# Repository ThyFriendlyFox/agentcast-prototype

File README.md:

# Agentcast

An HDMI dongle with a far-field mic array. Plug it into any TV; people in
the room talk, a cloud agent does the work, and the TV shows the results.
The product spec is [`docs/office-agent-dongle.md`](docs/office-agent-dongle.md).

## Hardware versions

| Version | State | Boards | Notes |
|---|---|---|---|
| [v0.5](hardware/v0.5/) | in work | an 80 x 30 mm, 8-layer stick with our own computer (ESP32-P4), LT8912B HDMI bridge, ESP32-C6 Wi-Fi, XUNPU HDMI-003 male plug, mic, mute, USB-C power and USB-C mic port | Not yet ordered: firmware and the LT8912B crystal value are open. |
| [v0.4](hardware/v0.4/) | archived | the v0.3 stick with a male HDMI Type-A plug on its end: plugs straight into the TV | Gates GREEN. Plug footprint awaits the plug's drawing (4 numbers). Not yet ordered. |
| [v0.3](hardware/v0.3/) | archived | one board, 67 x 46 mm stick: CM5 carrier, HDMI-A at the end, USB-C power and USB-C external mic on the sides, on-board mic, hardware mute | Gates GREEN. CM5 position checked against Raspberry Pi's 3D model. Fab files in `hardware/v0.3/dongle/fab/`. Not yet ordered. |
| [v0.2](hardware/v0.2/) | archived | one board, 57 x 50.4 mm: CM5 carrier, HDMI-A, USB-C power, USB-C port for an external mic, on-board mic, hardware mute | Gates GREEN. Fab files in `hardware/v0.2/dongle/fab/`. Not yet ordered. |
| [v0.1](hardware/v0.1/) | archived | main (CM5 carrier) and mic bar (4 mics) on a cable | Gates GREEN on both boards. Never ordered. |

## Tools

The boards are designed as code and checked with the
[Via EE Workcenter](https://github.com/ThyFriendlyFox/via): KiCad 10,
ngspice and FreeRouting, driven by `workcenter`. Each board folder holds a
`design.py`; the KiCad files beside it are generated from it.

```bash
make verify
```

## How work is run

[`agent-kit/ROUTING.md`](agent-kit/ROUTING.md) says which file governs
which job. Agents read [`CLAUDE.md`](CLAUDE.md) first.

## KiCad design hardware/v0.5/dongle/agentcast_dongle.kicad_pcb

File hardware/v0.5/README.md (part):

# Agentcast dongle v0.5

> **In work.** Made from [v0.4](../v0.4/) (commit `223e73b`). v0.5 drops the
> Raspberry Pi CM5 and puts our own small computer on a Chromecast-sized stick.

One board, **80 x 30 mm**, 8 layers, parts on both faces. A male HDMI plug
(XUNPU HDMI-003) clamps one end; the Wi-Fi antenna is at the other.

| | v0.4 | v0.5 |
|---|---|---|
| Size | 67 x 46 mm | 80 x 30 mm |
| Computer | Raspberry Pi CM5 module (55 x 40 mm, Linux) | ESP32-P4 (10 x 10 mm, 32 MB PSRAM in the package, no Linux) |
| HDMI | from the CM5 | LT8912B MIPI DSI to HDMI bridge, with HDMI audio |
| Wi-Fi | the CM5's | ESP32-C6-MINI-1 module (Wi-Fi 6), SDIO to the P4 |
| HDMI plug footprint | HDMI Type-A layout, 4 numbers unconfirmed | the XUNPU HDMI-003 drawing, every number |
| Layers | 4 | 8 (F.Cu, In1 GND, In2-In5, In6 GND, B.Cu), JLCPCB JLC081611-2116 |

| Top | Bottom | Turning |
|---|---|---|
|  |  |  |

Schematic: [`dongle/docs/schematic.png`](dongle/docs/schematic.png).

## Why no full computer

The dongle's jobs (spec, "How it works") are: hear the room and stream it to
the cloud agent, show what the agent made on the TV, and play the agent's
voice. The cloud does the thinking. None of that needs Linux or a browser on
the stick:

| Job | v0.5 |
|---|---|
| Hear the room | ICS-43434 I2S mic (or a USB mic on J6), streamed over Wi-Fi |
| Show the work | The cloud renders the dashboard and sends frames (JPEG, decoded by the P4's hardware JPEG codec); the P4 drives HDMI through DSI at 720p60 or 1080p30 |
| Speak | I2S audio into the LT8912B, out over HDMI to the TV's speakers |
| Echo cancellation | Mic capture and HDMI playback run on the same I2S clock (one BCLK, one WS) |
| Mute | SW2 cuts the power of both mics; LIVE / MUTED LEDs run from the switch |

What it gives up: the stick cannot run a web page by itself, so the cloud
renders the screen. A 2-lane DSI link at 1.5 Gb/s per lane (ESP32-P4 datasheet
4.2.1.7) carries 720p60 or 1080p30, not 4K.

## Parts

| Ref | Part | Why |
|---|---|---|
| U1 | Espressif ESP32-P4NRW32, QFN104 | 2 x RISC-V 400 MHz, 32 MB PSRAM in the package (no DDR to route), MIPI DSI, I2S, USB 2.0 HS, JPEG codec, H.264 encoder |
| U4 | Winbond W25Q128JVPIQ, WSON-8 | 16 MB flash for the firmware; top face, under the P4's flash pins |
| Y1 | 40 MHz, +/-10 ppm, 3225 | The P4 firmware supports 40 MHz only (Espressif hardware design guidelines, HDG 1.4.2) |
| U5, L1 | TI TLV62569 + 2.2 uH | The P4's core supply, under the P4's own control (EN_DCDC, FB_DCDC), exactly HDG Fig. 5 |
| U3 | Lontium LT8912B, QFN64 | MIPI DSI to HDMI 1.4 with I2S audio input |
| Y2 | crystal, 3225 | The LT8912B wants one on XTALI/XTALO; its datasheet gives no frequency (Open item 2) |
| U2 | Espressif ESP32-C6-MINI-1 | Wi-Fi 6, certified module with its antenna; SDIO slave on GPIO18-23 (ESP32-C6 datasheet, IO MUX) |
| J3, J3B | XUNPU HDMI-003 male HDMI-A plug | Clamps a 1.60 mm board; even contacts on top, odd on the bottom (manufacturer drawing) |
| J4 | GCT USB4085 USB-C | Power (5 V, 5.1k Rd on each CC) and the P4's USB serial/JTAG for flashing |
| J6 | GCT USB4085 USB-C | Host port for an external USB mic, on the P4's USB 2.0 HS; power via U11, which the mute switch enables |
| U9, L2 | TI TLV62569 + 2.2 uH | +3V3 from +5V, 0.6 V x (1 + 100k / 22.1k) = 3.31 V |
| U6 | TI TLV75518 | +1V8 for the LT8912B and the P4's IO bank 6 |
| U12 | Diodes AP2112K-1.8 | MIC_1V8 from the mute-switched MIC_3V3 |
| U7, U11 | TI TPS2051C | HDMI +5V (EN +3V3) and the external mic's VBUS (EN MIC_3V3); current limit and reverse blocking |
| Q1, Q2 | BSS138 | DDC (EDID) level shift, 5 V at the plug to 3.3 V at the P4 |
| U8 / U10 | USBLC6-2SC6 / TPD2EUSB30 | ESD on J4's full-speed pair / J6's high-speed pair (0.7 pF; HDG asks for under 1 pF on HS) |
| MK1 | TDK ICS-43434 | I2S mic, on MIC_1V8 |
| U13, U14 | 74LVC1G34 | Clock buffers on MIC_1V8: a muted mic gets no power through its clock pins (Ioff) |
| SW2 | C&K PCM12 | Mute slide switch, out of the long side |
| SW1, SW3 | Omron B3U | BOOT (GPIO35) and RESET (CHIP_PU), bottom face |

## Voltage domains

The LT8912B's I2C, I2S and reset pins are 1.8 V CMOS (LT8912B datasheet
Table 6.2.1). The P4 powers each GPIO bank separately (HDG, "HP/LP IO Power
Supply"), so bank 6 (GPIO49-54, VDD_IO_6) runs at 1.8 V and carries every
LT8912B and mic signal; the other banks run at 3.3 V.

| Rail | From | Feeds |
|---|---|---|
| +5V | J4 | U9, U7 (HDMI +5V), U11 (J6 VBUS), PWR LED |
| +3V3 | U9 | P4 VDD_LP, VDD_IO_0/4/5, VDD_ANA, VDD_BAT, VDD_LDO, VDD_DCDCC, VDD_USBPHY; C6; U5, U6 |
| VDD_HP (about 1.1 V) | U5 | P4 VDD_HP_0-3 |
| +1V8 | U6 | LT8912B, P4 VDD_IO_6 |
| VDDO_FLASH | P4's flash LDO (3.3 V default) | P4 VDD_FLASHIO, U4 |
| VDDO_PSRAM | P4's PSRAM LDO | P4 VDD_PSRAM_0/1 |
| VDD_MIPI | P4's VDDO_3, set to 2.5 V in firmware | P4 VDD_MIPI_DPHY (HDG: 2.25-2.75 V, internal regulator recommended) |
| MIC_3V3 | SW2 from +3V3 | U12, U11's enable, LIVE LED, MIC_LIVE sense |
| MIC_1V8 | U12 | MK1, U13, U14 |

## Pin plan (ESP32-P4)

From the ESP32-P4 datasheet v0.7 (Table 2-1) and the HDG. Every signal on a
GPIO goes through the GPIO matrix except USB serial/JTAG (GPIO24/25, IO MUX).

Signals the GPIO matrix can put anywhere sit on every other free pin, on the
side facing what they drive: neighbouring signal pins at 0.35 mm pitch leave
no room for their vias.

| GPIO (pin) | Bank | Net | Function |
|---|---|---|---|
| 10 / 12 (11 / 13) | 0, 3.3 V | C6_RXD / C6_TXD | UART to the C6, for flashing it from the P4 |
| 14 (15) | 0 | C6_BOOT | the C6's GPIO9 strap, open drain, 10k up |
| 16 (17) | 0 | C6_EN | C6 enable, open drain, 10k up + 1 uF |
| 17 (18) | 0 | LT_RST_N | LT8912B reset, open drain, 10k up to +1V8 |
| 18-23 (19, 20, 22-25) | 0 | SDIO_CLK, CMD, D0-D3 | SD/MMC host slot 2 (GPIO matrix) to the C6; 22 ohm series, 10k up (HDG 1.3.11) |
| 24 / 25 (52 / 53) | 4 | USB_FS_DN / DP | USB serial/JTAG to J4, 22 ohm series (HDG 1.3.12) |
| 27 (56) | 4 | MIC_LIVE | input, high = mics powered |
| 29 (58) | 4 | STATE_LED | amber STATE LED |
| 31 / 32 (61 / 63) | 4 | DDC_SDA_3V3 / SCL | I2C to the TV's EDID through Q1 / Q2 |
| 35 (66) | 4 | BOOT | strapping: low at reset = download mode (HDG Table 4); 10k up, SW1 |
| 36 (68) | 4 | GPIO36_PU | strapping, 10k up |
| 46 (88) | 5 | HDMI_CEC | CEC, open drain, 27k up to +3V3 |
| 49 / 50 (92 / 93) | 6, 1.8 V | LT_SDA / LT_SCL | I2C to the LT8912B, 4.7k up to +1V8 |
| 51 / 52 (94 / 95) | 6 | I2S_BCLK / I2S_WS | I2S master clocks: LT8912B and (through U13 / U14) the mic |
| 53 (97) | 6 | I2S_DOUT | I2S data to the LT8912B (HDMI audio) |
| 54 (98) | 6 | I2S_DIN | I2S data from the mic, 100k down |
| DSI (35-40) | - | DSI_D0, D1, CK | to the LT8912B's MIPIRX0, MIPIRX1, CK |
| USB HS (49 / 50) | - | USB_HS_DN / DP | J6 through U10 |

CEC goes straight from a P4 pin to the plug: the LT8912B's CEC pin (58) is
also its I2S data input, and the stick needs HDMI audio more.

## HDMI plug

The plug's footprint (`library/gen_library.py`) follows the XUNPU HDMI-003
drawing's recommended PCB layout: 0.70 mm pads at 1.00 mm pitch, 3.00 mm long,
even pins on the top face and odd on the bottom; shell tabs 2.20 x 2.20 mm on
top and 3.05 x 2.20 mm underneath, 13.60 mm apart; two 0.60 x 0.80 mm slots in
the board edge at the tabs (`StickDesign` cuts them). One change: the pads stop
0.30 mm short of the edge, the board's copper-to-edge rule. The drawing's slots
are plated; these are plain cuts, and the shell is soldered at its four tabs.

## Stackup and pairs

8 layers, 1.6 mm, JLCPCB's JLC081611-2116: F.Cu signal, In1.Cu GND plane,
In2.Cu to In5.Cu signal, In6.Cu GND plane, B.Cu signal. The 0.35 mm pitch of
the P4 did not route on 4 layers (20-38 connections left open on every try),
nor on 6 layers at 26 or 30 mm wide (26-31 left open), nor on 8 layers at
72 mm long (23 left open); "Layout and routing" says what closed the rest. The prepreg under each
outer layer is 0.109 mm of 2116 (er 4.16), so the pairs are narrow:

| Pairs | Width / gap | Differential impedance |
|---|---|---|
| TMDS (LT8912B to the plug), F.Cu over In1 | 0.12 / 0.16 mm | about 104 ohm |
| DSI (P4 to LT8912B), F.Cu over In1 | 0.14 / 0.21 mm (the P4's 0.35 mm pad pitch) | about 102 ohm |

Check both against JLCPCB's impedance calculator when ordering: kicadgen
writes a generic stackup into the board file and has no way to set this one,
so the board file's stackup table is not the one to order.

The four TMDS pairs run 9.3-9.7 mm from the LT8912B to the plug. D1 and CK end
on the top contacts; D2 and D0 drop through a via pair to the bottom contacts.
Skew within each pair: 0.000 mm.

The three DSI pairs are drawn by hand (`route_dsi` in `design.py`), not by
the router: they leave the P4's bottom row, run under it as a U and climb into
the LT8912B's bottom row. CK crosses D1 on In2.Cu through four vias. Lengths
21.5-28.8 mm; skew within a pair: D0 1.16 mm, D1 1.16 mm, CK 2.14 mm.

**Firmware must swap the polarity of DSI data lanes D0 and D1** in the
LT8912B: their P and N are crossed on the board so the pairs do not cross each
other. The LT8912B datasheet lists its data lanes as "polarity swappable".

## Layout and routing

80 x 30 mm. The P4 has 62 signal and supply pins at 0.35 mm pitch, and the
ring around it is where every route failed. What made it route:

- **Room.** The board grew from 72 x 26 mm to 80 x 30 mm. The mic, its LDO and
  its clock buffers sit in the gap left of the P4, by its I2S pins; the P4's
  bulk capacitors stand 1 mm off its pins.
- **Pin plan.** Signals the GPIO matrix can move sit on every other free pin,
  facing what they drive (Pin plan).
- **Fanout** (`fanout` in `design.py`). Before routing, each P4 and LT8912B
  pin gets a via: runs of neighbouring pins splay at 45 degrees into one row of
  vias 0.6 mm apart (no track has to pass between two vias, which at this pitch
  it cannot); a path search takes pins the fan cannot reach; pins boxed in
  outside take a via inward, in the 0.85 mm between the pad ring and the
  exposed pad, where the bottom-face decoupling caps step aside for them.
  All but two of the P4's pins (29 and 72) get one, the flash pins drawn by
  hand aside, and all but one of the LT8912B's (59); the router joins those.
- **Flash.** U4 sits on the top face under the P4's flash pins, turned so its
  near row runs VCC, HOLD, CK, D like pins 30-33; those four are drawn by hand
  (`route_flash`), each in its own lane, and pins 27-29 take vias above the
  lanes. The bus needs no via in the P4's busiest corner.
- **HDMI D0** runs 0.6 mm further before its jog, which opens a via spot for
  the LT8912B's +1V8 pin 26, boxed in between D1 and D0 until then.
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
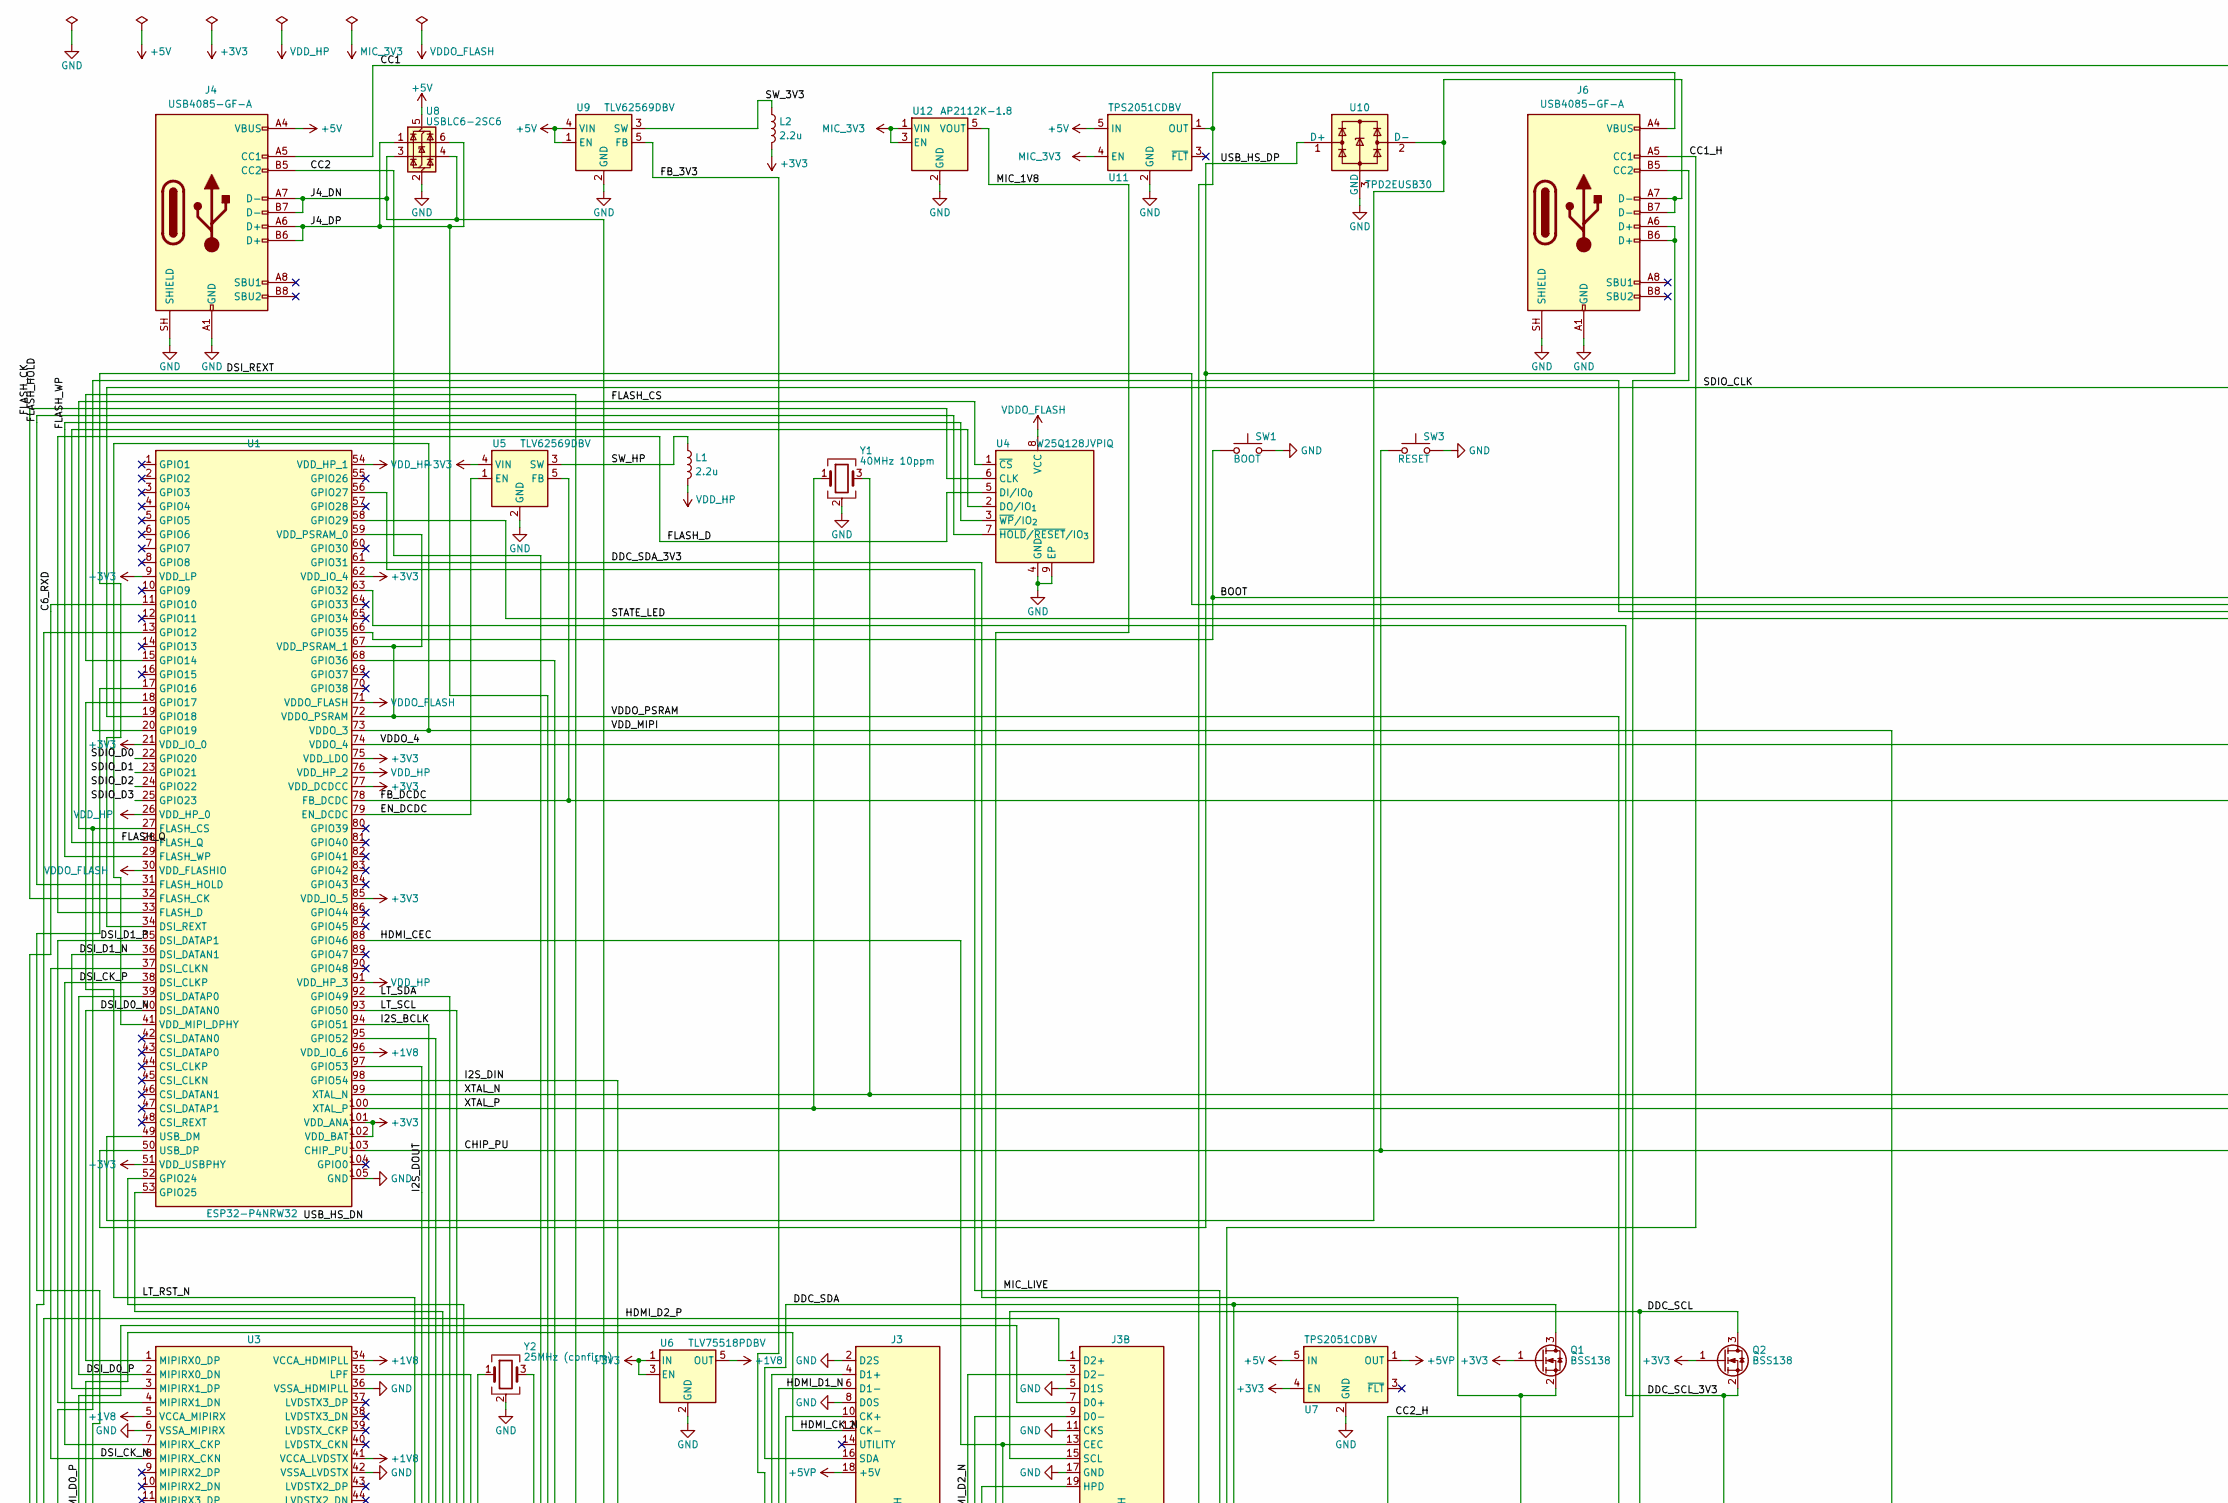
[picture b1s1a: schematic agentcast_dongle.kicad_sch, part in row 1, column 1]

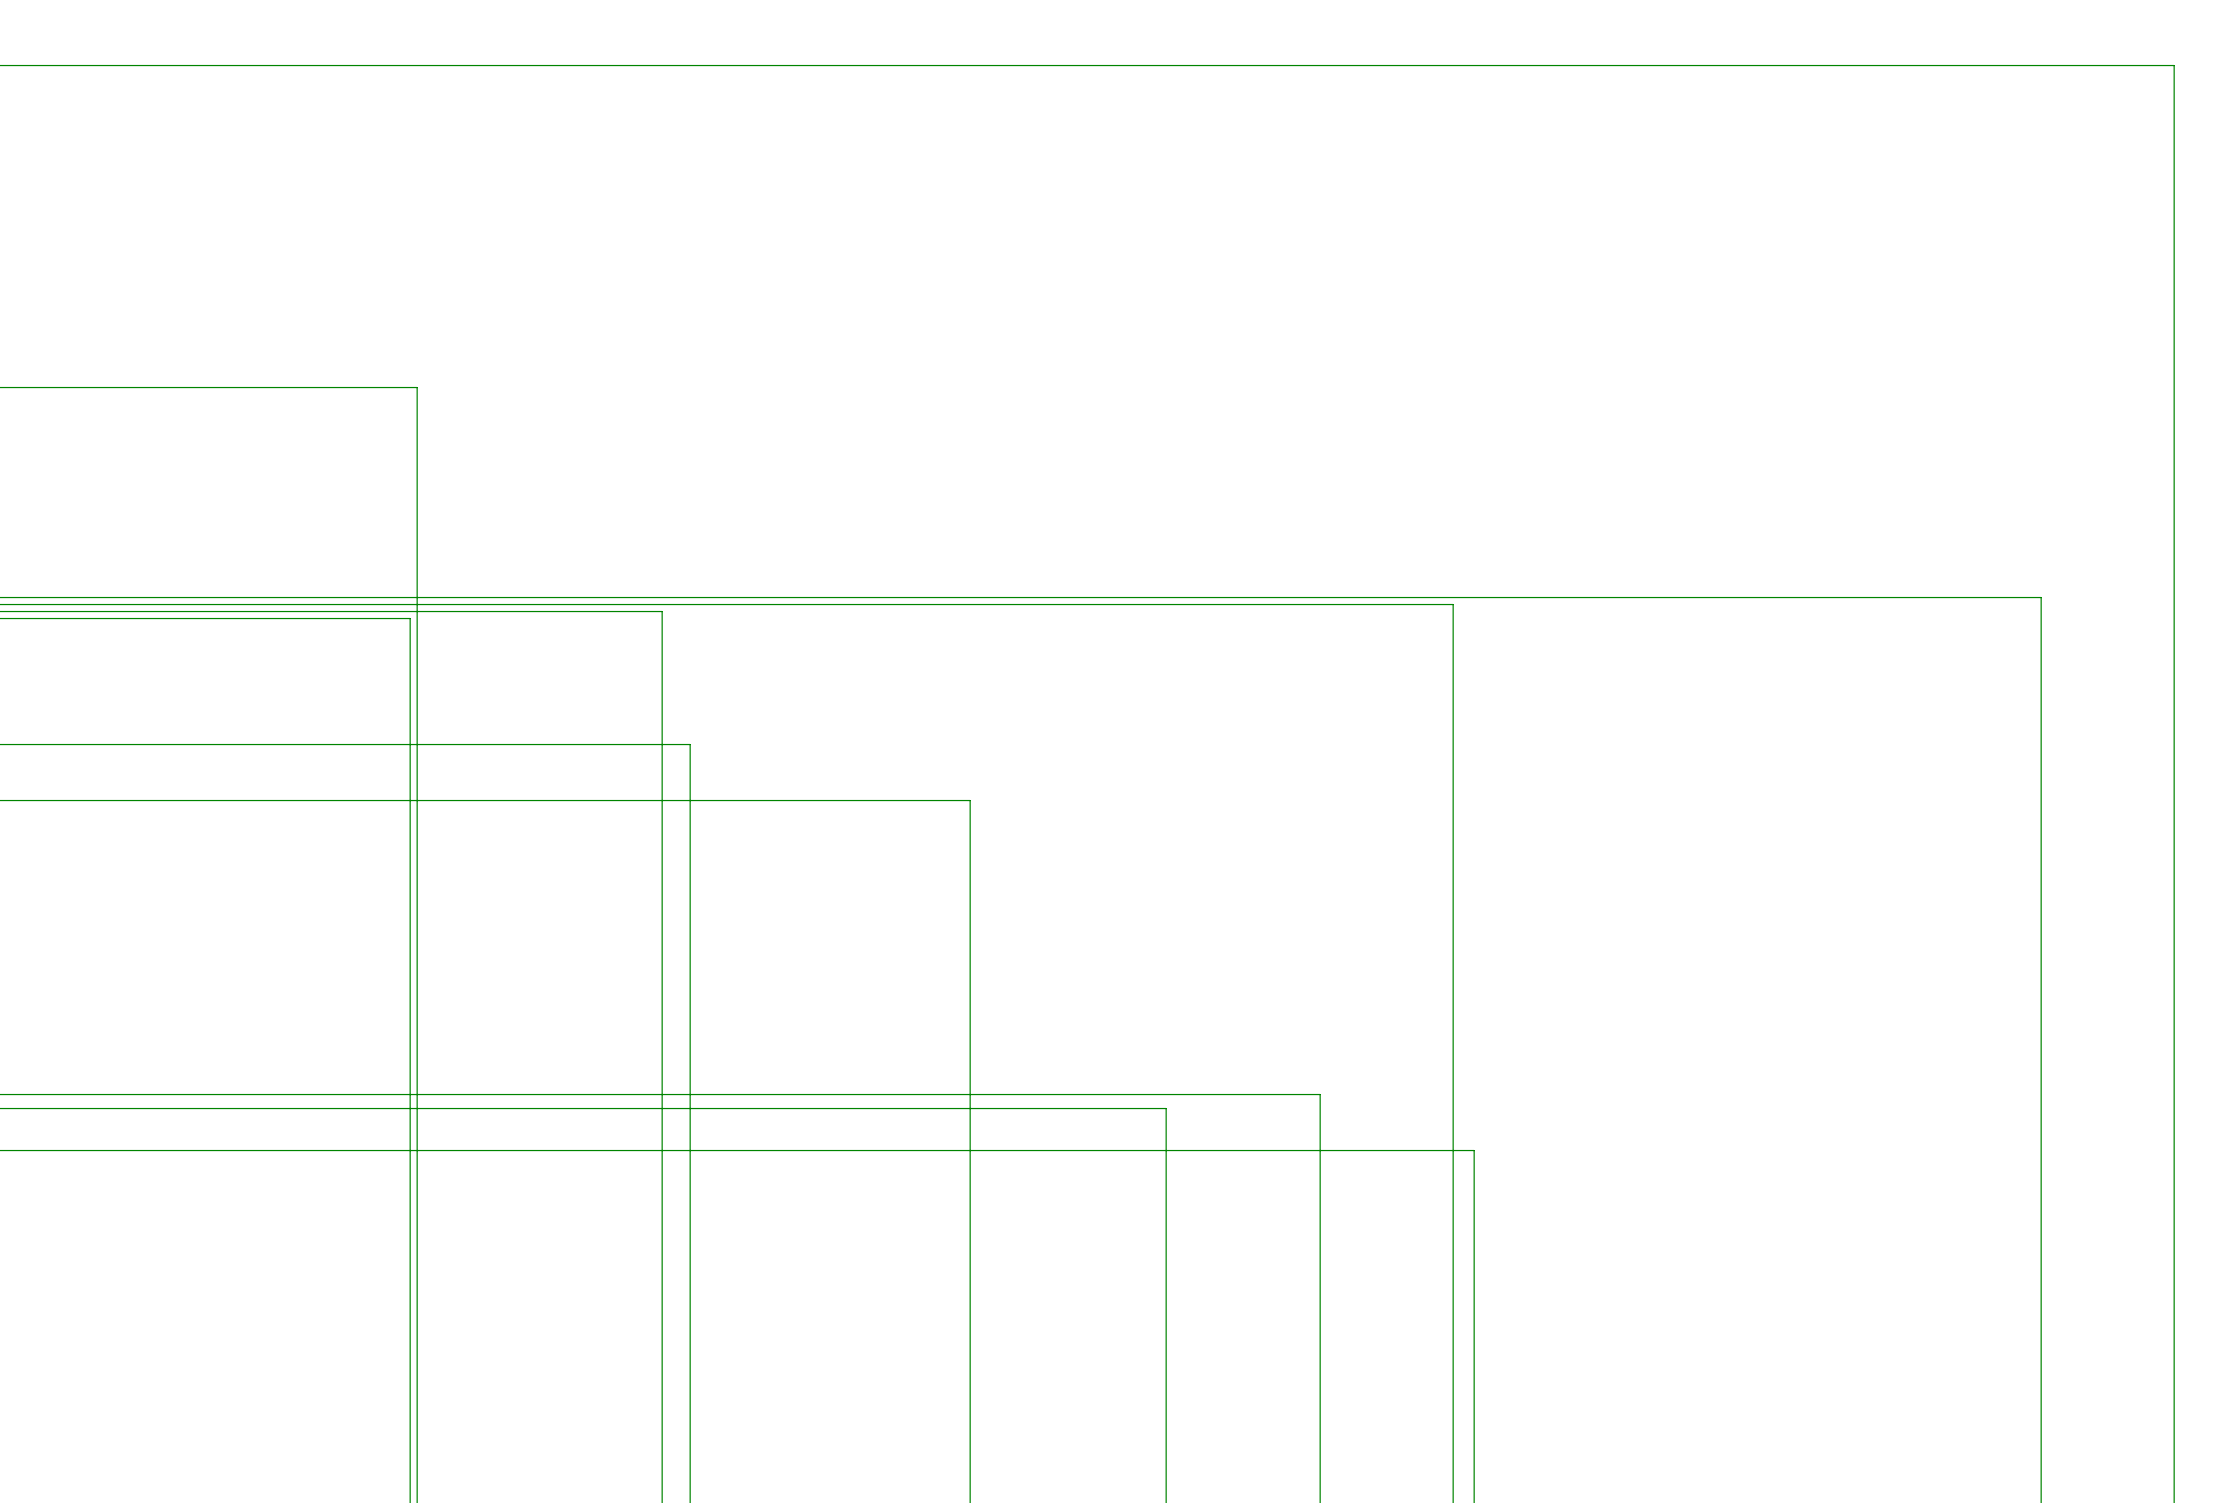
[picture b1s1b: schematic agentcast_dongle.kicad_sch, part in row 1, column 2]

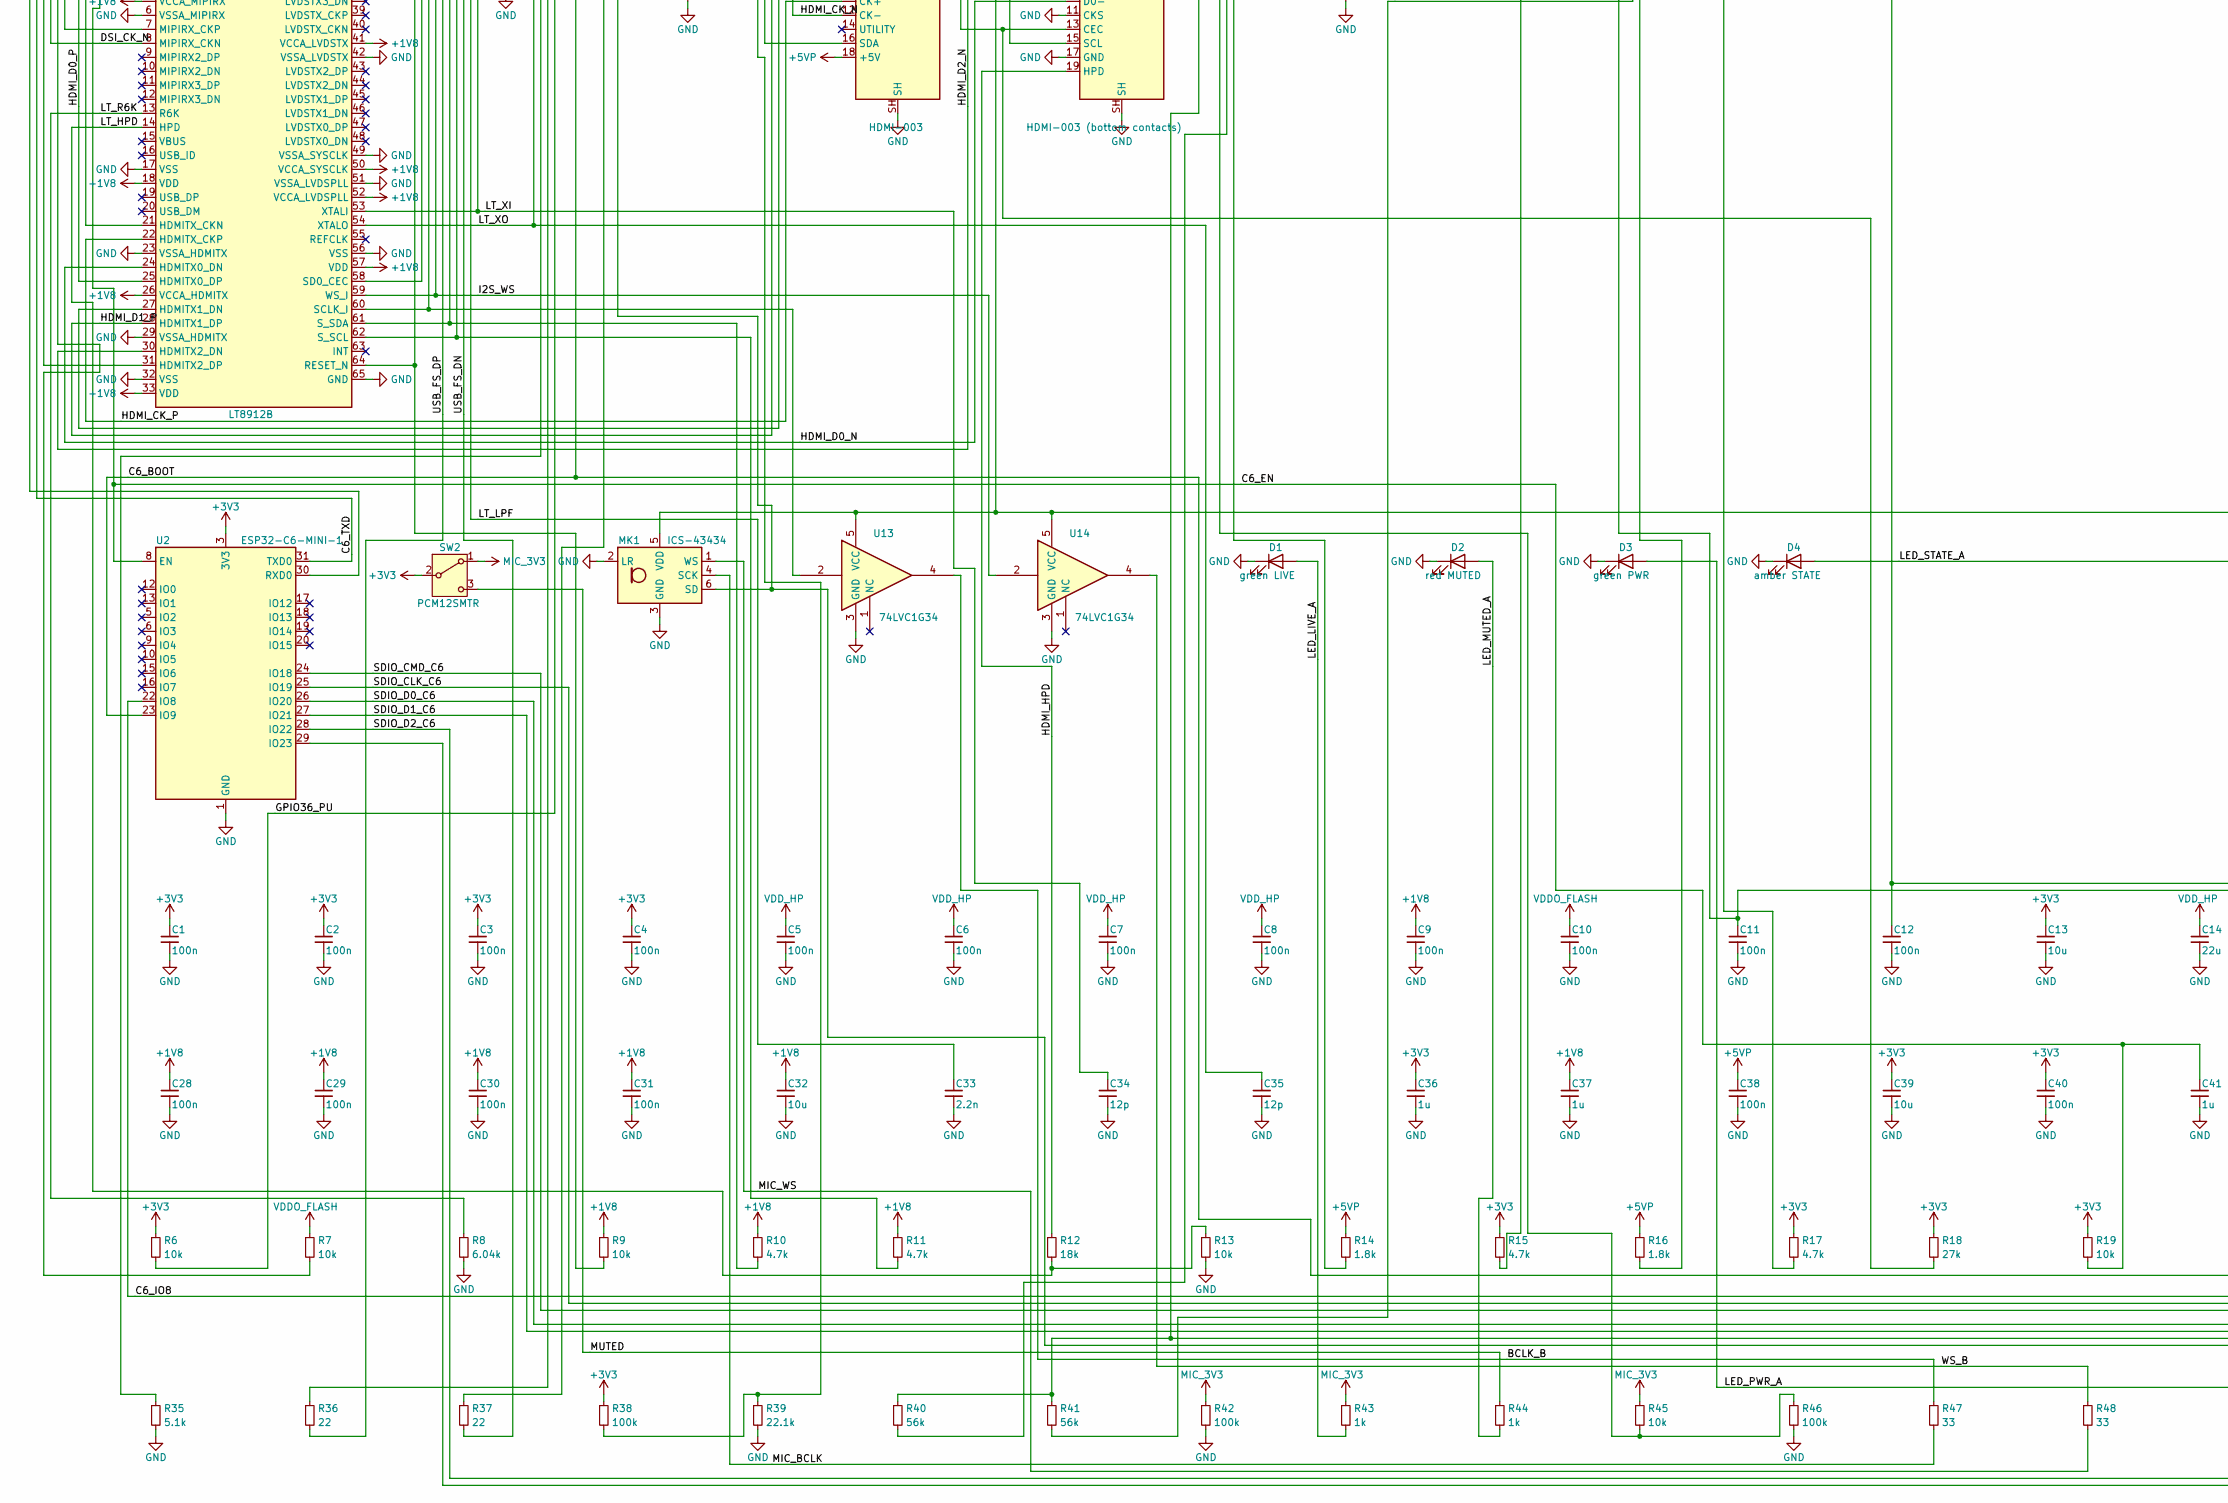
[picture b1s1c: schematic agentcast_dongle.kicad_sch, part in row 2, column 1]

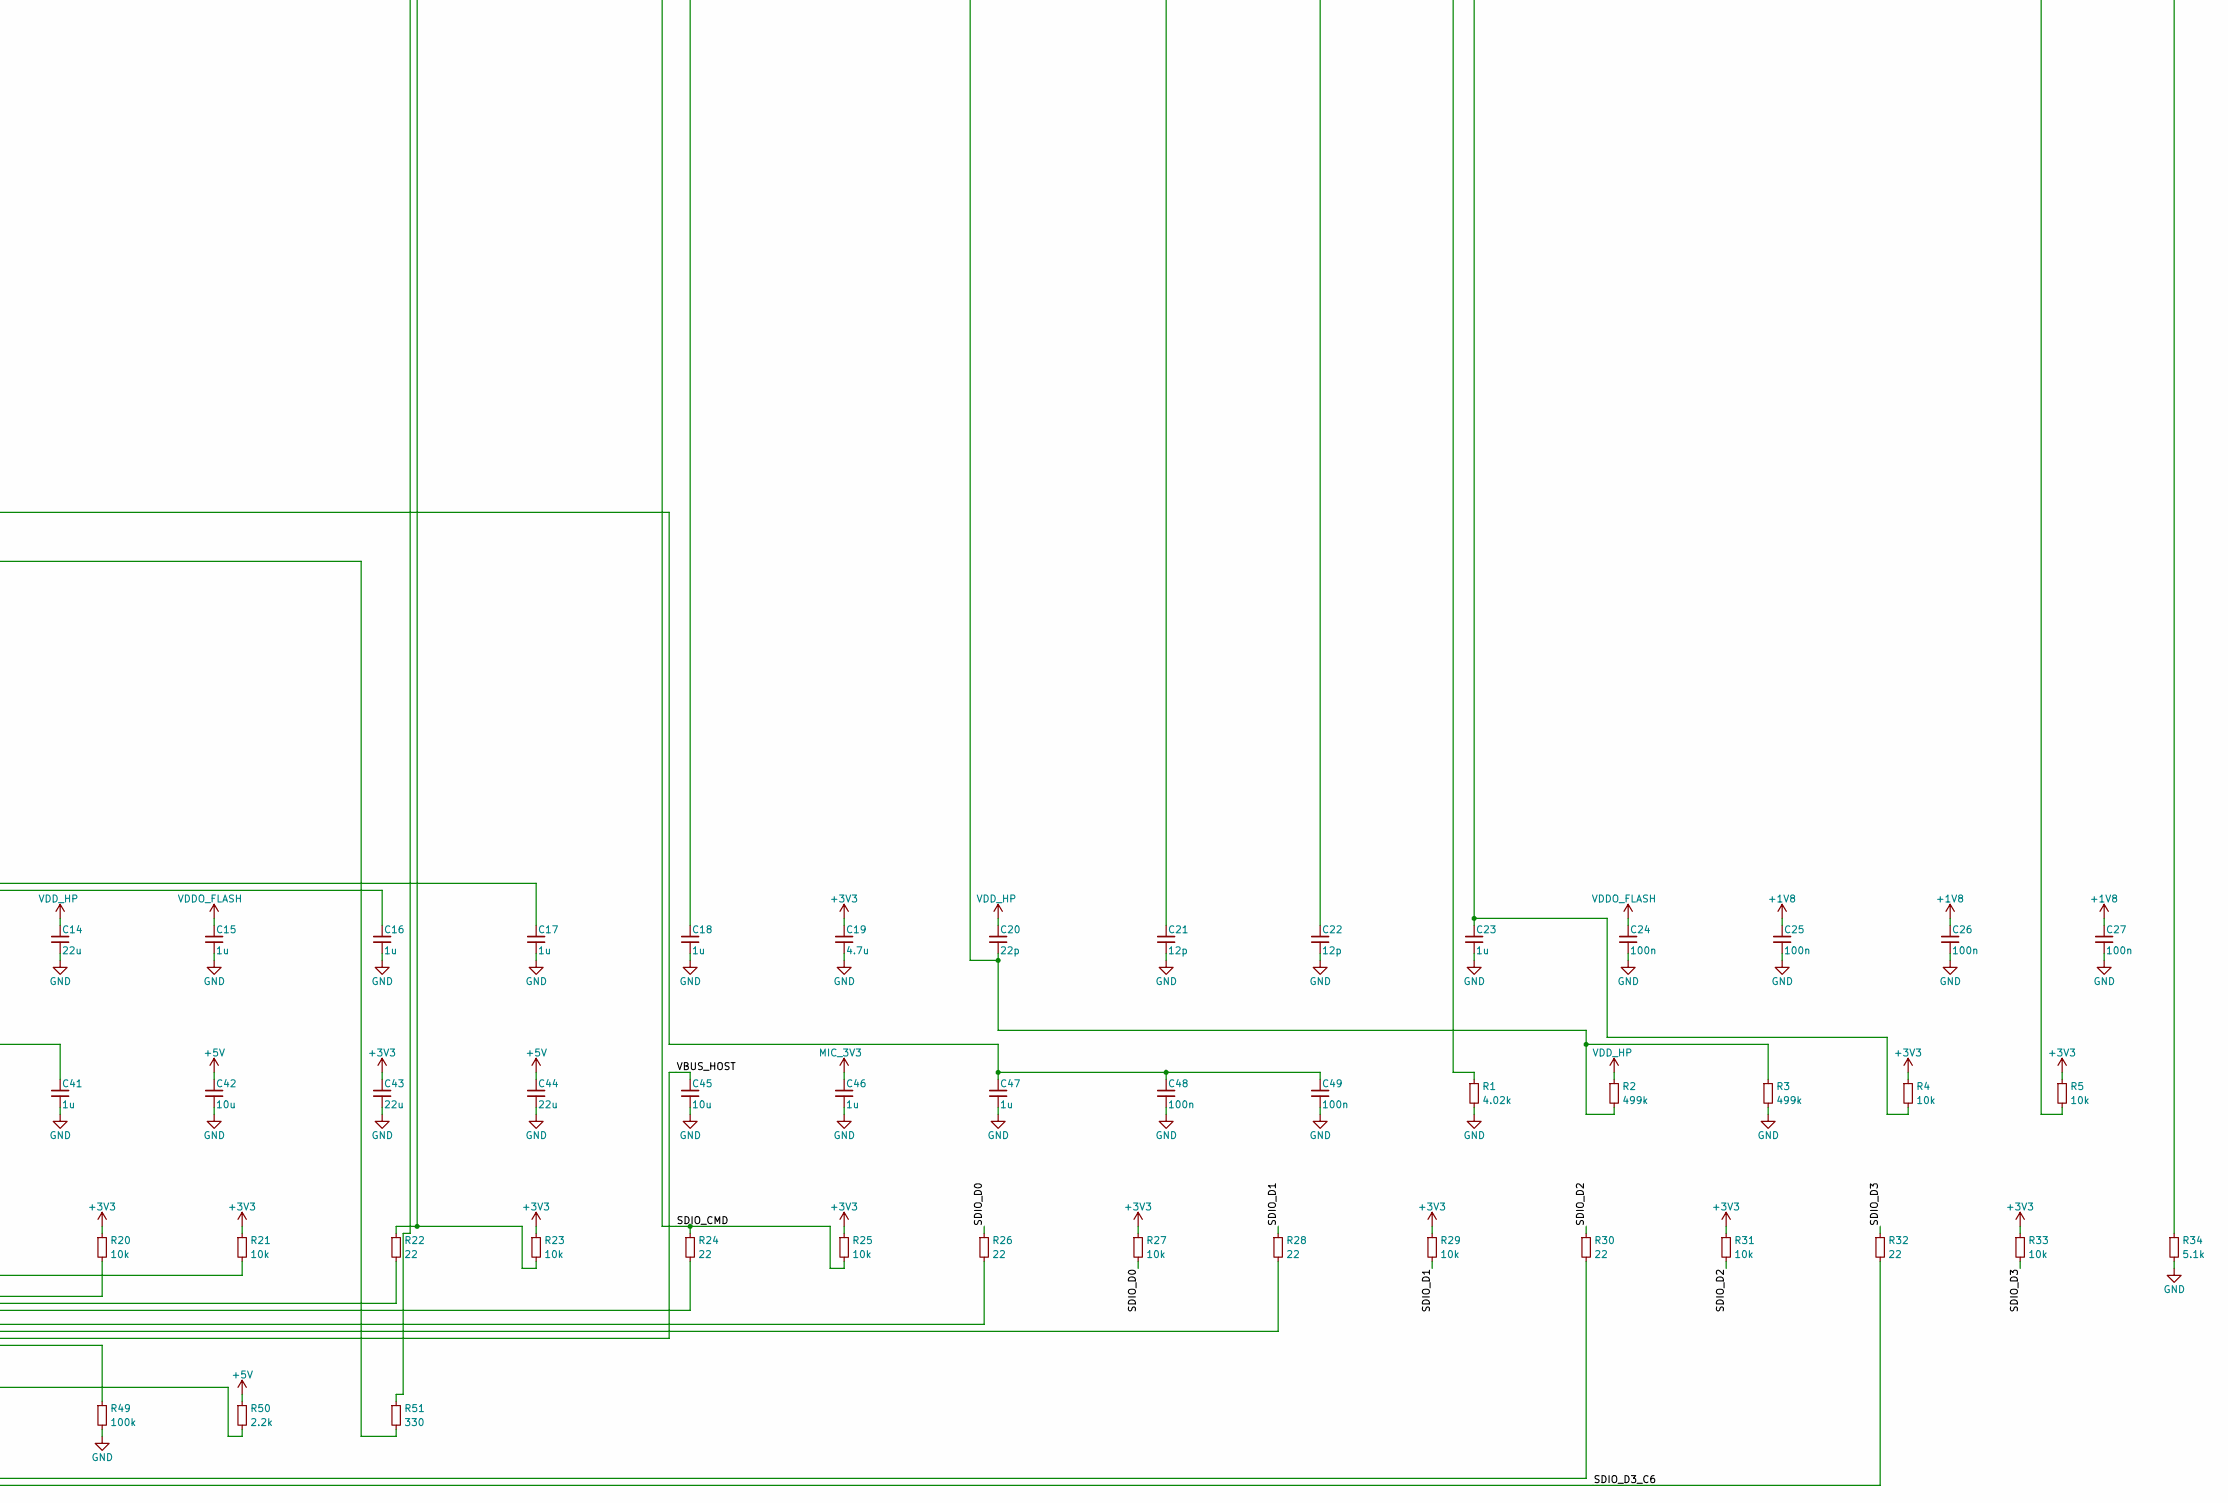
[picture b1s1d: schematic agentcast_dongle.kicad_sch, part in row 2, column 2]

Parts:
C1, C2, C3, C4, C5, C6, C7, C8, C9, C10, C11, C12, C24, C25, C26, C27, C28, C29, C30, C31, C38, C40, C48, C49: 100n; C_0402_1005Metric
C13, C32, C39, C42, C45: 10u; C_0603_1608Metric
C14, C43, C44: 22u; C_0805_2012Metric
C15, C16, C17, C18, C23, C36, C37, C41, C46, C47: 1u; C_0402_1005Metric
C19: 4.7u; C_0603_1608Metric
C20: 22p; C_0402_1005Metric
C21, C22, C34, C35: 12p; C_0402_1005Metric
C33: 2.2n; C_0402_1005Metric
D1: green LIVE; LED_0603_1608Metric
D2: red MUTED; LED_0603_1608Metric
D3: green PWR; LED_0603_1608Metric
D4: amber STATE; LED_0603_1608Metric
J3: HDMI-003; HDMI_A_Plug_XUNPU_HDMI-003_Top
J3B: HDMI-003 (bottom contacts); HDMI_A_Plug_XUNPU_HDMI-003_Bottom
J4, J6: USB4085-GF-A; USB_C_Receptacle_GCT_USB4085
L1, L2: 2.2u; L_1008_2520Metric
MK1: ICS-43434; InvenSense_ICS-43434-6_3.5x2.65mm
Q1, Q2: BSS138; SOT-23
R1: 4.02k; R_0402_1005Metric
R2, R3: 499k; R_0402_1005Metric
R4, R5, R6, R7, R9, R13, R19, R20, R21, R23, R25, R27, R29, R31, R33, R45: 10k; R_0402_1005Metric
R8: 6.04k; R_0402_1005Metric
R10, R11, R15, R17: 4.7k; R_0402_1005Metric
R12: 18k; R_0402_1005Metric
R14, R16: 1.8k; R_0402_1005Metric
R18: 27k; R_0402_1005Metric
R22, R24, R26, R28, R30, R32, R36, R37: 22; R_0402_1005Metric
R34, R35: 5.1k; R_0402_1005Metric
R38, R42, R46, R49: 100k; R_0402_1005Metric
R39: 22.1k; R_0402_1005Metric
R40, R41: 56k; R_0402_1005Metric
R43, R44: 1k; R_0402_1005Metric
R47, R48: 33; R_0402_1005Metric
R50: 2.2k; R_0402_1005Metric
R51: 330; R_0402_1005Metric
SW1: BOOT; SW_SPST_B3U-1000P
SW2: PCM12SMTR; SW_SPDT_PCM12
SW3: RESET; SW_SPST_B3U-1000P
U1: ESP32-P4NRW32; QFN-104-1EP_10x10mm_P0.35mm_EP7.5x7.5mm
U2: ESP32-C6-MINI-1
U3: LT8912B; QFN-64-1EP_7.5x7.5mm_P0.4mm_EP6.2x6.2mm
U4: W25Q128JVPIQ; WSON-8-1EP_6x5mm_P1.27mm_EP3.4x4.3mm
U5, U9: TLV62569DBV; SOT-23-5
U6: TLV75518PDBV; SOT-23-5
U7, U11: TPS2051CDBV; SOT-23-5
U8: USBLC6-2SC6; SOT-23-6
U10: TPD2EUSB30; Texas_DRT-3
U12: AP2112K-1.8; SOT-23-5
U13, U14: 74LVC1G34; SOT-353_SC-70-5
Y1: 40MHz 10ppm; Crystal_SMD_3225-4Pin_3.2x2.5mm
Y2: 25MHz (confirm); Crystal_SMD_3225-4Pin_3.2x2.5mm

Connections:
+1V8: C9.1, C25.1, C26.1, C27.1, C28.1, C29.1, C30.1, C31.1, C32.1, C37.1, R9.1, R10.1, R11.1, U1.96 (VDD_IO_6), U3.5 (VCCA_MIPIRX), U3.18 (VDD), U3.26 (VCCA_HDMITX), U3.33 (VDD), U3.34 (VCCA_HDMIPLL), U3.41 (VCCA_LVDSTX), U3.50 (VCCA_SYSCLK), U3.52 (VCCA_LVDSPLL), U3.57 (VDD), U6.5 (OUT)
+3V3: C1.1, C2.1, C3.1, C4.1, C13.1, C19.1, C36.1, C39.1, C40.1, C43.1, L2.2, Q1.1 (G), Q2.1 (G), R4.1, R5.1, R6.1, R15.1, R17.1, R18.1, R19.1, R20.1, R21.1, R23.1, R25.1, R27.1, R29.1, R31.1, R33.1, R38.1, SW2.2 (B), U1.9 (VDD_LP), U1.21 (VDD_IO_0), U1.51 (VDD_USBPHY), U1.62 (VDD_IO_4), U1.75 (VDD_LDO), U1.77 (VDD_DCDCC), U1.85 (VDD_IO_5), U1.101 (VDD_ANA), U1.102 (VDD_BAT), U2.3 (3V3), U5.4 (VIN), U6.1 (IN), U6.3 (EN), U7.4 (EN)
+5V: C42.1, C44.1, J4.A4 (VBUS), J4.A9 (VBUS), J4.B4 (VBUS), J4.B9 (VBUS), R50.1, U7.5 (IN), U8.5 (VBUS), U9.1 (EN), U9.4 (VIN), U11.5 (IN)
+5VP: C38.1, J3.18 (+5V), R14.1, R16.1, U7.1 (OUT)
/BCLK_B: R47.1, U13.4
/BOOT: R5.2, SW1.1, U1.66 (GPIO35)
/C6_BOOT: R21.2, U1.15 (GPIO14), U2.23 (IO9)
/C6_EN: C41.1, R19.2, U1.17 (GPIO16), U2.8 (EN)
/C6_IO8: R20.2, U2.22 (IO8)
/C6_RXD: U1.11 (GPIO10), U2.30 (RXD0)
/C6_TXD: U1.13 (GPIO12), U2.31 (TXD0)
/CC1: J4.A5 (CC1), R34.1
/CC1_H: J6.A5 (CC1), R40.2
/CC2: J4.B5 (CC2), R35.1
/CC2_H: J6.B5 (CC2), R41.2
/CHIP_PU: C23.1, R4.2, SW3.1, U1.103 (CHIP_PU)
/DDC_SCL: J3B.15 (SCL), Q2.3 (D), R16.2
/DDC_SCL_3V3: Q2.2 (S), R17.2, U1.63 (GPIO32)
/DDC_SDA: J3.16 (SDA), Q1.3 (D), R14.2
/DDC_SDA_3V3: Q1.2 (S), R15.2, U1.61 (GPIO31)
/DSI_CK_N: U1.37 (DSI_CLKN), U3.8 (MIPIRX_CKN)
/DSI_CK_P: U1.38 (DSI_CLKP), U3.7 (MIPIRX_CKP)
/DSI_D0_N: U1.40 (DSI_DATAN0), U3.1 (MIPIRX0_DP)
/DSI_D0_P: U1.39 (DSI_DATAP0), U3.2 (MIPIRX0_DN)
/DSI_D1_N: U1.36 (DSI_DATAN1), U3.3 (MIPIRX1_DP)
/DSI_D1_P: U1.35 (DSI_DATAP1), U3.4 (MIPIRX1_DN)
/DSI_REXT: R1.1, U1.34 (DSI_REXT)
/EN_DCDC: U1.79 (EN_DCDC), U5.1 (EN)
/FB_3V3: R38.2, R39.1, U9.5 (FB)
/FB_DCDC: C20.2, R2.2, R3.1, U1.78 (FB_DCDC), U5.5 (FB)
/FLASH_CK: U1.32 (FLASH_CK), U4.6 (CLK)
/FLASH_CS: R7.2, U1.27 (FLASH_CS), U4.1 (~CS)
/FLASH_D: U1.33 (FLASH_D), U4.5 (DI/IO_{0})
/FLASH_HOLD: U1.31 (FLASH_HOLD), U4.7 (~HOLD/~RESET/IO_{3})
/FLASH_Q: U1.28 (FLASH_Q), U4.2 (DO/IO_{1})
/FLASH_WP: U1.29 (FLASH_WP), U4.3 (~WP/IO_{2})
/GPIO36_PU: R6.2, U1.68 (GPIO36)
/HDMI_CEC: J3B.13 (CEC), R18.2, U1.88 (GPIO46)
/HDMI_CK_N: J3.12 (CK-), U3.21 (HDMITX_CKN)
/HDMI_CK_P: J3.10 (CK+), U3.22 (HDMITX_CKP)
/HDMI_D0_N: J3B.9 (D0-), U3.24 (HDMITX0_DN)
/HDMI_D0_P: J3B.7 (D0+), U3.25 (HDMITX0_DP)
/HDMI_D1_N: J3.6 (D1-), U3.27 (HDMITX1_DN)
/HDMI_D1_P: J3.4 (D1+), U3.28 (HDMITX1_DP)
/HDMI_D2_N: J3B.3 (D2-), U3.30 (HDMITX2_DN)
/HDMI_D2_P: J3B.1 (D2+), U3.31 (HDMITX2_DP)
/HDMI_HPD: J3B.19 (HPD), R12.1
/I2S_BCLK: U1.94 (GPIO51), U3.60 (SCLK_I), U13.2
/I2S_DIN: MK1.6 (SD), R49.1, U1.98 (GPIO54)
/I2S_DOUT: U1.97 (GPIO53), U3.58 (SD0_CEC)
/I2S_WS: U1.95 (GPIO52), U3.59 (WS_I), U14.2
/J4_DN: J4.A7 (D-), J4.B7 (D-), R37.1, U8.3 (I/O2), U8.4 (I/O2)
/J4_DP: J4.A6 (D+), J4.B6 (D+), R36.1, U8.1 (I/O1), U8.6 (I/O1)
/LED_LIVE_A: D1.2 (A), R43.2
/LED_MUTED_A: D2.2 (A), R44.2
/LED_PWR_A: D3.2 (A), R50.2
/LED_STATE_A: D4.2 (A), R51.2
/LT_HPD: R12.2, R13.1, U3.14 (HPD)
/LT_LPF: C33.1, U3.35 (LPF)
/LT_R6K: R8.1, U3.13 (R6K)
/LT_RST_N: R9.2, U1.18 (GPIO17), U3.64 (RESET_N)
/LT_SCL: R11.2, U1.93 (GPIO50), U3.62 (S_SCL)
/LT_SDA: R10.2, U1.92 (GPIO49), U3.61 (S_SDA)
/LT_XI: C34.1, U3.53 (XTALI), Y2.1
/LT_XO: C35.1, U3.54 (XTALO), Y2.3
/MIC_1V8: C47.1, C48.1, C49.1, MK1.5 (VDD), U12.5 (VOUT), U13.5 (VCC), U14.5 (VCC)
/MIC_BCLK: MK1.4 (SCK), R47.2
/MIC_LIVE: R45.2, R46.1, U1.56 (GPIO27)
/MIC_WS: MK1.1 (WS), R48.2
/MUTED: R44.1, SW2.3 (C)
/SDIO_CLK: R22.1, R23.2, U1.19 (GPIO18)
/SDIO_CLK_C6: R22.2, U2.25 (IO19)
/SDIO_CMD: R24.1, R25.2, U1.20 (GPIO19)
/SDIO_CMD_C6: R24.2, U2.24 (IO18)
/SDIO_D0: R26.1, R27.2, U1.22 (GPIO20)
/SDIO_D0_C6: R26.2, U2.26 (IO20)
/SDIO_D1: R28.1, R29.2, U1.23 (GPIO21)
/SDIO_D1_C6: R28.2, U2.27 (IO21)
/SDIO_D2: R30.1, R31.2, U1.24 (GPIO22)
/SDIO_D2_C6: R30.2, U2.28 (IO22)
/SDIO_D3: R32.1, R33.2, U1.25 (GPIO23)
/SDIO_D3_C6: R32.2, U2.29 (IO23)
/STATE_LED: R51.1, U1.58 (GPIO29)
/SW_3V3: L2.1, U9.3 (SW)
/SW_HP: L1.1, U5.3 (SW)
/USB_FS_DN: R37.2, U1.52 (GPIO24)
/USB_FS_DP: R36.2, U1.53 (GPIO25)
/USB_HS_DN: J6.A7 (D-), J6.B7 (D-), U1.49 (USB_DM), U10.2 (D-)
/USB_HS_DP: J6.A6 (D+), J6.B6 (D+), U1.50 (USB_DP), U10.1 (D+)
/VBUS_HOST: C45.1, J6.A4 (VBUS), J6.A9 (VBUS), J6.B4 (VBUS), J6.B9 (VBUS), R40.1, R41.1, U11.1 (OUT)
/VDDO_4: C18.1, U1.74 (VDDO_4)
/VDDO_PSRAM: C11.1, C16.1, U1.59 (VDD_PSRAM_0), U1.67 (VDD_PSRAM_1), U1.72 (VDDO_PSRAM)
/VDD_MIPI: C12.1, C17.1, U1.41 (VDD_MIPI_DPHY), U1.73 (VDDO_3)
/WS_B: R48.1, U14.4
/XTAL_N: C22.1, U1.99 (XTAL_N), Y1.3
/XTAL_P: C21.1, U1.100 (XTAL_P), Y1.1
GND: C1.2, C2.2, C3.2, C4.2, C5.2, C6.2, C7.2, C8.2, C9.2, C10.2, C11.2, C12.2, C13.2, C14.2, C15.2, C16.2, C17.2, C18.2, C19.2, C21.2, C22.2, C23.2, C24.2, C25.2, C26.2, C27.2, C28.2, C29.2, C30.2, C31.2, C32.2, C33.2, C34.2, C35.2, C36.2, C37.2, C38.2, C39.2, C40.2, C41.2, C42.2, C43.2, C44.2, C45.2, C46.2, C47.2, C48.2, C49.2, D1.1 (K), D2.1 (K), D3.1 (K), D4.1 (K), J3.2 (D2S), J3.8 (D0S), J3.SH, J3B.5 (D1S), J3B.11 (CKS), J3B.17 (GND), J3B.SH, J4.A1 (GND), J4.A12 (GND), J4.B1 (GND), J4.B12 (GND), J4.SH (SHIELD), J6.A1 (GND), J6.A12 (GND), J6.B1 (GND), J6.B12 (GND), J6.SH (SHIELD), MK1.2 (LR), MK1.3 (GND), R1.2, R3.2, R8.2, R13.2, R34.2, R35.2, R39.2, R42.2, R46.2, R49.2, SW1.2, SW3.2, U1.105 (GND), U2.1 (GND), U2.2 (GND), U2.11 (GND), U2.14 (GND), U2.36 (GND), U2.37 (GND), U2.38 (GND), U2.39 (GND), U2.40 (GND), U2.41 (GND), U2.42 (GND), U2.43 (GND), U2.44 (GND), U2.45 (GND), U2.46 (GND), U2.47 (GND), U2.48 (GND), U2.49 (GND), U2.50 (GND), U2.51 (GND), U2.52 (GND), U2.53 (GND), U3.6 (VSSA_MIPIRX), U3.17 (VSS), U3.23 (VSSA_HDMITX), U3.29 (VSSA_HDMITX), U3.32 (VSS), U3.36 (VSSA_HDMIPLL), U3.42 (VSSA_LVDSTX), U3.49 (VSSA_SYSCLK), U3.51 (VSSA_LVDSPLL), U3.56 (VSS), U3.65 (GND), U4.4 (GND), U4.9 (EP), U5.2 (GND), U6.2 (GND), U7.2 (GND), U8.2 (GND), U9.2 (GND), U10.3 (GND), U11.2 (GND), U12.2 (GND), U13.3 (GND), U14.3 (GND), Y1.2 (G), Y1.4 (G), Y2.2 (G), Y2.4 (G)
MIC_3V3: C46.1, R42.1, R43.1, R45.1, SW2.1 (A), U11.4 (EN), U12.1 (VIN), U12.3 (EN)
VDDO_FLASH: C10.1, C15.1, C24.1, R7.1, U1.30 (VDD_FLASHIO), U1.71 (VDDO_FLASH), U4.8 (VCC)
VDD_HP: C5.1, C6.1, C7.1, C8.1, C14.1, C20.1, L1.2, R2.1, U1.26 (VDD_HP_0), U1.54 (VDD_HP_1), U1.76 (VDD_HP_2), U1.91 (VDD_HP_3)
